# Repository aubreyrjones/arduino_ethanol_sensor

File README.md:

Arduino Ethanol Controller
--------------------------

This is Arduino software for an automotive ethanol fuel sensor controller.

The ethanol sensor is designed to give real-time readings of ethanol content
in fuel as a percentage between 0 and 100%. It outputs this as an FM signal
from 50-150Hz, with the ethanol content given by subtracting 50 from the
signal frequency. The sensor itself runs on 12V, but outputs a 5V signal.
It also outputs fuel temperature readings, which are not used in this
project.

When adding an ethanol sensor to a vehicle that does not already support flex
fuel, there is unlikely to be an ECU input natively compatible with the
sensor's FM output. Instead, only a 0-5V analog input will be available. This
project converts the sensor signal to a voltage that the ECU can accept.

# Features

* Converts 50-150Hz square wave FM to a 0.5-4.5V signal
* Voltages below 0.5V and above 4.5V are used for error states (can be used to set DTC)
* "Sane" ethanol values within milliseconds of power-on from persistent memory
* All floating point math is `constexpr`, with no floating point operations occuring at runtime.

# Design

Depends on 16MHz/5V Arduino. CPU frequency is assumed fixed, with timing values computed
from CPU ticks.

This code assumes you are using an [I2C 12-bit DAC](https://www.sparkfun.com/products/12918) 
and a [I2C FRAM](https://www.adafruit.com/product/1895). Those links are to the breakout
boards used in prototyping this project's hardware. If you use those boards, be aware that
both of them have I2C pullup resistors. It is recommended that you desolder the pullup
resistors from the Adafruit board.

The FRAM chip/board may be omitted without altering the software. This will only affect 
the first fraction of a second after power up but before the sensor's 
readings have stabilized.

Electrical connection is simple. Wire the I2C lines, in parallel, to SDA/SCL of the Arduino.
The breakout boards can be stacked and soldered on a pair of header pins on the I2C, and short
wires for power. The breakout boards must be powered at 5V.

Wire the ethanol sensor to D8, with a 4.7kOhm pullup resistor in parallel. The ethanol sensor
should be powered at 12V.

Wire the DAC output to the ECU input.

The schematic below accurately describes the prototype circuit I have installed in my vehicle. 
The board design included in this repository is currently untested.

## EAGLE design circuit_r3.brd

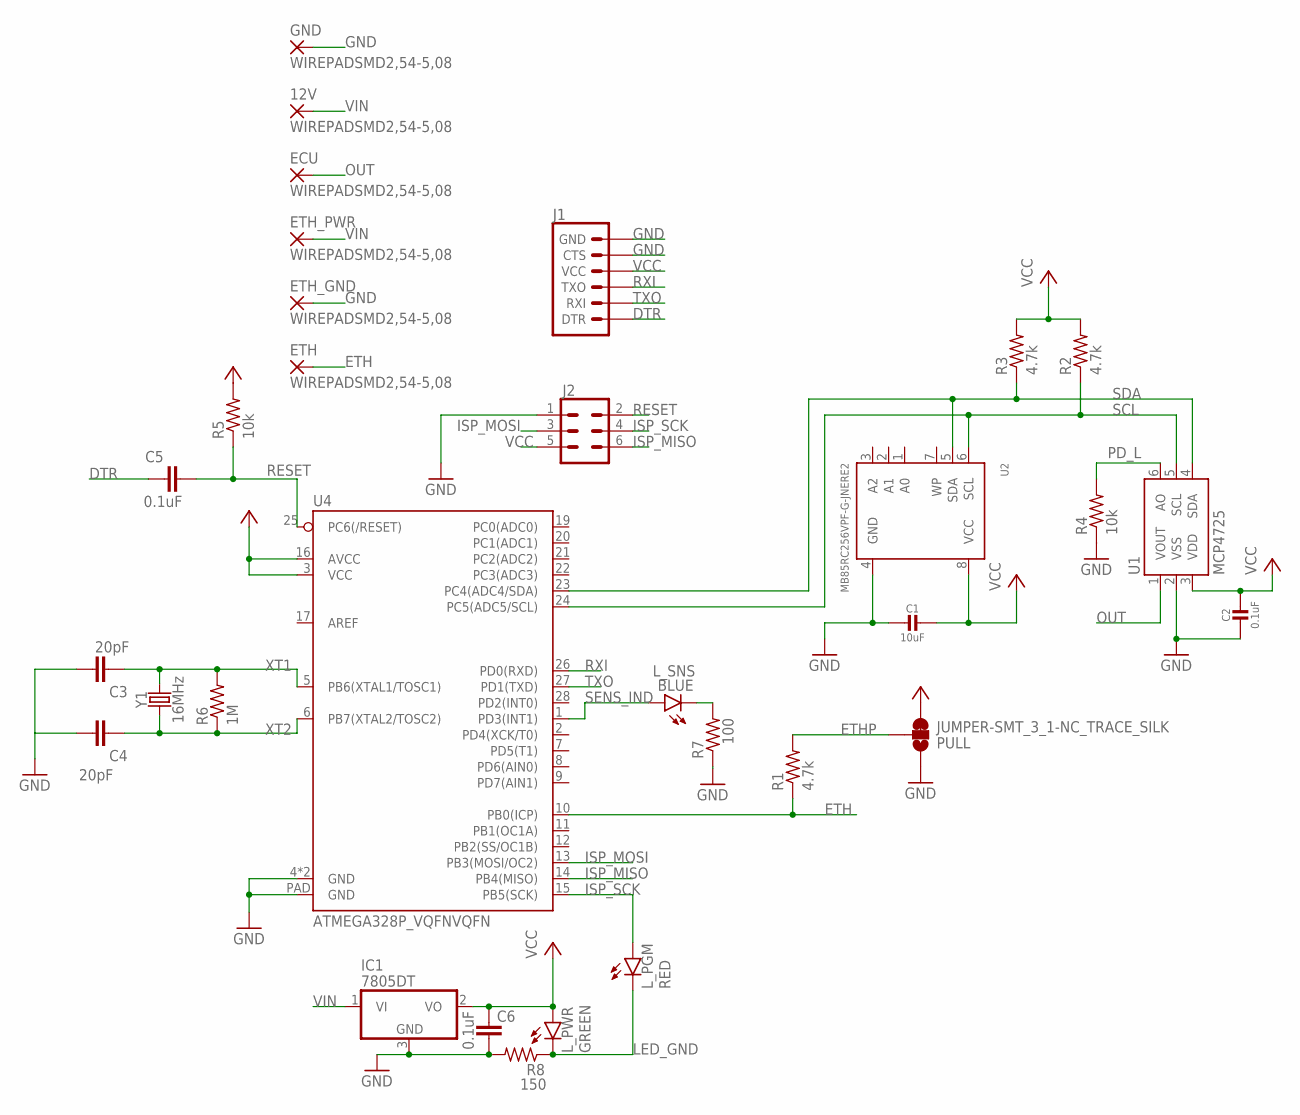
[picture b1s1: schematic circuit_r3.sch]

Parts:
12V: WIREPADSMD2,54-5,08; SMD2,54-5,08
C1: 10uF; _0805
C2: 0.1uF; _0603
C3, C4: 20pF; 0603
C5, C6: 0.1uF; 0603
ECU: WIREPADSMD2,54-5,08; SMD2,54-5,08
ETH: WIREPADSMD2,54-5,08; SMD2,54-5,08
ETH_GND: WIREPADSMD2,54-5,08; SMD2,54-5,08
ETH_PWR: WIREPADSMD2,54-5,08; SMD2,54-5,08
GND: WIREPADSMD2,54-5,08; SMD2,54-5,08
IC1: 7805DT; TO252
J1: 6_PIN_SERIAL_TARGETSILK; 6_PIN_SERIAL_TARGET_SIDE_W_SILK
J2: CONN_03X22X3_SILK_MALE_PTH; 2X3
L_PGM: RED; LED-0603
L_PWR: GREEN; LED-0603
L_SNS: BLUE; LED-0603
PULL: JUMPER-SMT_3_1-NC_TRACE_SILK; SMT-JUMPER_3_1-NC_TRACE_SILK
R1, R2, R3: 4.7k; R0603
R4, R5: 10k; R0603
R6: 1M; R0603
R7: 100; R0603
R8: 150; R0603
U1: MCP4725; SOT23-6
U2: MB85RC256VPF-G-JNERE2; SOIC8_208MIL
U4: ATMEGA328P_VQFNVQFN; VQFN-28
Y1: 16MHz; CRYSTAL-SMD-5X3.2-4PAD

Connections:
DTR: C5.2, J1.P$1 (DTR)
ETH: ETH.1, R1.1, U4.10 (PB0(ICP))
ETHP: PULL.2, R1.2
GND: C1.2, C2.2, C3.1, C4.1, C6.1, ETH_GND.1, GND.1, IC1.3 (GND), J1.P$5 (CTS), J1.P$6 (GND), J2.1, PULL.1, R4.1, R7.1, R8.2, U1.2 (VSS), U2.4 (GND), U4.4 (GND), U4.18 (GND), U4.PAD (GND)
ISP_MISO: J2.6, U4.14 (PB4(MISO))
ISP_MOSI: J2.3, U4.13 (PB3(MOSI/OC2))
ISP_SCK: J2.4, L_PGM.A, U4.15 (PB5(SCK))
LED_GND: L_PGM.C, L_PWR.C, R8.1
unnamed: L_SNS.C, R7.2
OUT: ECU.1, U1.1 (VOUT)
PD_L: R4.2, U1.6 (AO)
RESET: C5.1, J2.2, R5.1, U4.25 (PC6(/RESET))
RXI: J1.P$2 (TXO), U4.26 (PD0(RXD))
SCL: R2.1, U1.5 (SCL), U2.6 (SCL), U4.24 (PC5(ADC5/SCL))
SDA: R3.1, U1.4 (SDA), U2.5 (SDA), U4.23 (PC4(ADC4/SDA))
SENS_IND: L_SNS.A, U4.1 (PD3(INT1))
TXO: J1.P$3 (RXI), U4.27 (PD1(TXD))
VCC: C1.1, C2.1, C6.2, IC1.2 (VO), J1.P$4 (VCC), J2.5, L_PWR.A, PULL.3, R2.2, R3.2, R5.2, U1.3 (VDD), U2.8 (VCC), U4.3 (VCC), U4.16 (AVCC)
VIN: 12V.1, ETH_PWR.1, IC1.1 (VI)
XT1: C3.2, R6.2, U4.5 (PB6(XTAL1/TOSC1)), Y1.3 (2)
XT2: C4.2, R6.1, U4.6 (PB7(XTAL2/TOSC2)), Y1.1

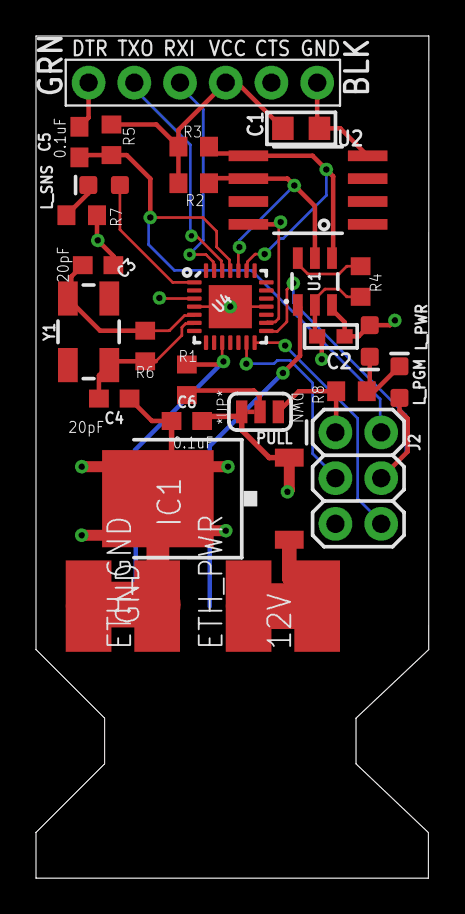
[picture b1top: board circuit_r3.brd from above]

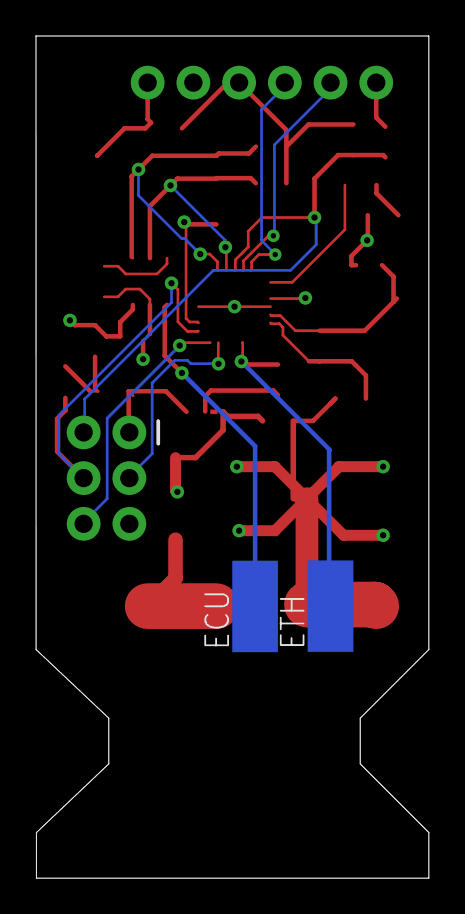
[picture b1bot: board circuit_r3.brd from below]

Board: 4 copper layers, 21.8 x 46.8 mm, 31 parts (2 on the bottom side), 21 nets.

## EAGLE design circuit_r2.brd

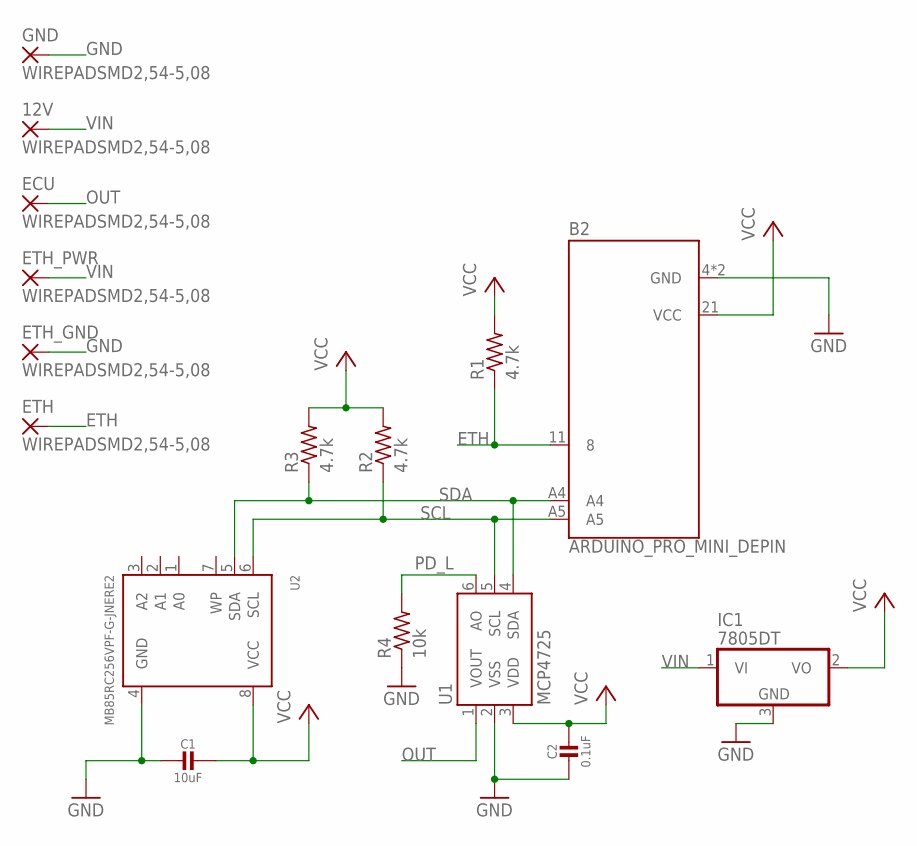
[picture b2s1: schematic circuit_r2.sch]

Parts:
12V: WIREPADSMD2,54-5,08; SMD2,54-5,08
B2: ARDUINO_PRO_MINI_DEPIN; ARDUINO_PRO_MINI
C1: 10uF; _0805MP
C2: 0.1uF; _0805MP
ECU: WIREPADSMD2,54-5,08; SMD2,54-5,08
ETH: WIREPADSMD2,54-5,08; SMD2,54-5,08
ETH_GND: WIREPADSMD2,54-5,08; SMD2,54-5,08
ETH_PWR: WIREPADSMD2,54-5,08; SMD2,54-5,08
GND: WIREPADSMD2,54-5,08; SMD2,54-5,08
IC1: 7805DT; TO252
R1, R2, R3: 4.7k; R0603
R4: 10k; R0603
U1: MCP4725; SOT23-6
U2: MB85RC256VPF-G-JNERE2; SOIC8_208MIL

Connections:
ETH: B2.11 (8), ETH.1, R1.1
GND: B2.4 (GND), B2.23 (GND), C1.2, C2.2, ETH_GND.1, GND.1, IC1.3 (GND), R4.1, U1.2 (VSS), U2.4 (GND)
OUT: ECU.1, U1.1 (VOUT)
PD_L: R4.2, U1.6 (AO)
SCL: B2.A5, R2.1, U1.5 (SCL), U2.6 (SCL)
SDA: B2.A4, R3.1, U1.4 (SDA), U2.5 (SDA)
VCC: B2.21 (VCC), C1.1, C2.1, IC1.2 (VO), R1.2, R2.2, R3.2, U1.3 (VDD), U2.8 (VCC)
VIN: 12V.1, ETH_PWR.1, IC1.1 (VI)

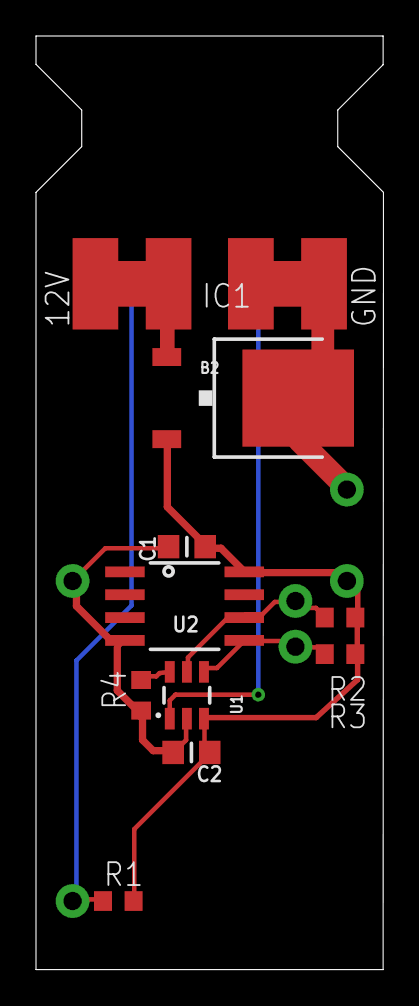
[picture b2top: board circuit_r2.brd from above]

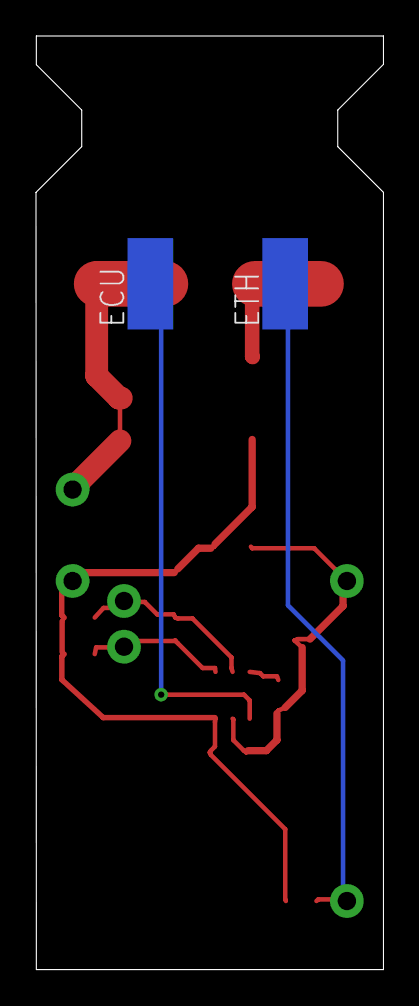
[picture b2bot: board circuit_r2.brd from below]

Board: 2 copper layers, 19.3 x 51.9 mm, 16 parts (2 on the bottom side), 8 nets.

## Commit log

2019-08-10 Lots of floating point.
2019-08-10 Updated to fixed point, constexpr, and better error handling.
2019-08-10 Math error.
2019-08-10 Added beginning of readme, partial circuit.
2019-08-10 Updated readme.
2019-08-10 Working on the schematic.
2019-08-11 Added schematic and board design.
2019-08-11 Added board preview.
2019-08-11 Eliminated stray `float`.
2019-08-11 Updated README to describe schematic and pcb state.
2019-08-11 Switched to rising edge pulse detection to avoid jitter from the PWM temp reading.
2019-08-24 Working on a version without the promini.
2019-08-24 Oooh, getting close.
2019-08-24 trying to make it smaller.
2019-08-24 pre autoroute
2019-08-24 More revisions...
2019-08-25 Pretty good design.
2019-08-26 Production prototype, including indicator leds.
2019-09-04 More fiddling with the r3 board.

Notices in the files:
parts and their libraries:
SparkFun-Boards-revised: Licensing: Creative Commons ShareAlike 4.0 International - https://creativecommons.org/licenses/by-sa/4.0
microbuilder: This work is placed in the public domain, and may be freely used for commercial and non-commercial work with the following conditions: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
